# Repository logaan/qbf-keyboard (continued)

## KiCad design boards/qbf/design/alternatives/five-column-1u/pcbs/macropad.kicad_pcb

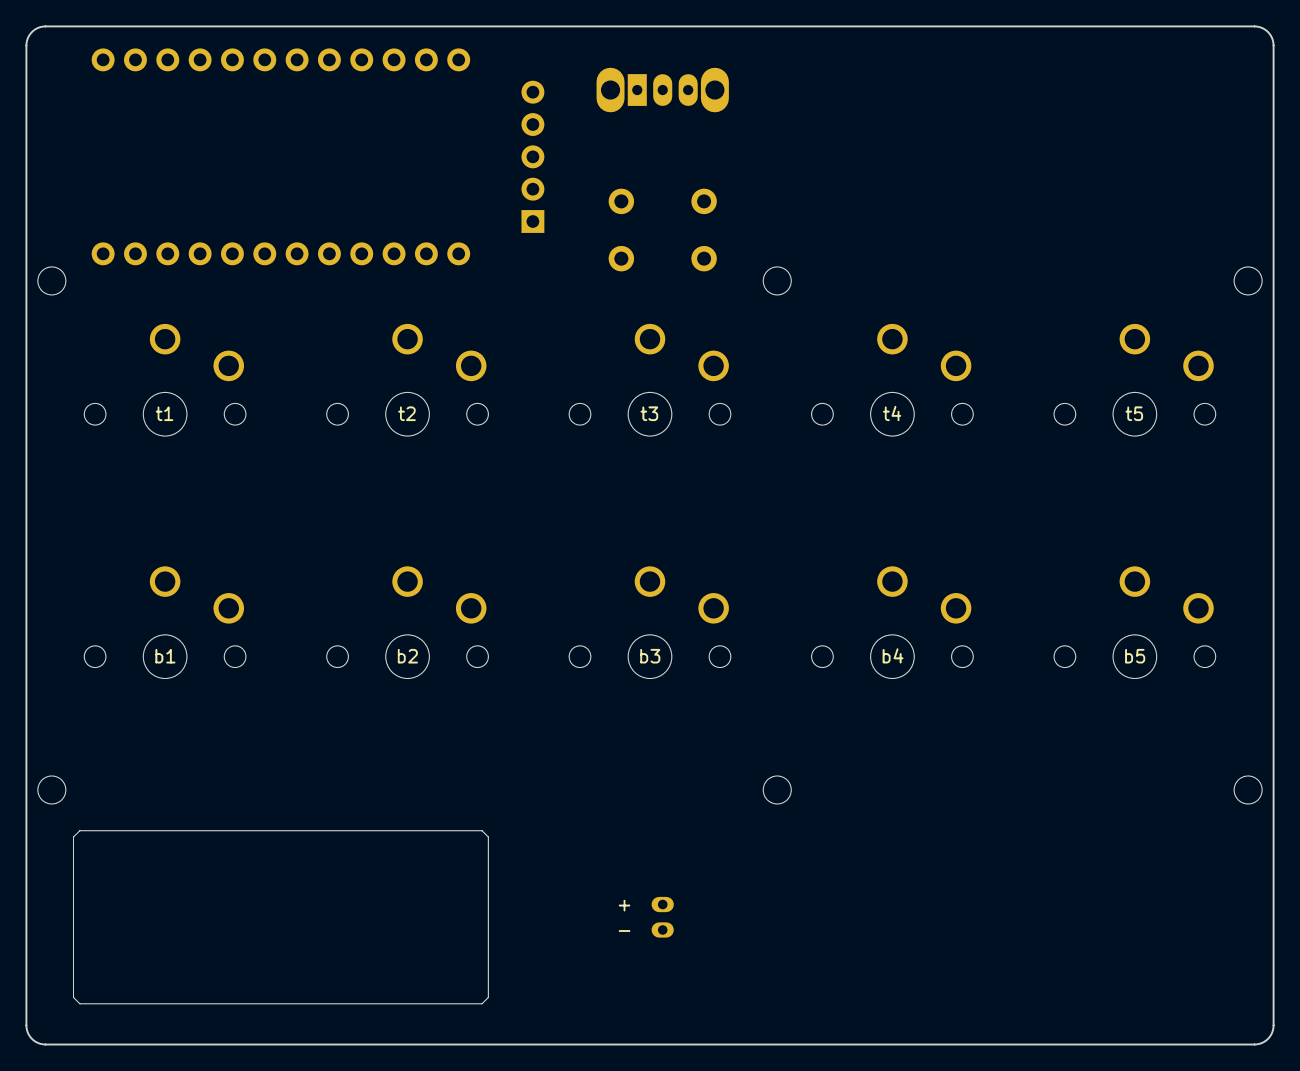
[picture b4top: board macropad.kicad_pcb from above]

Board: 2 copper layers, 98.0 x 80.0 mm, 23 parts (0 on the bottom side), 18 nets, no tracks yet.

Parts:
BAT1: 301230 110mAh max 32x13x3.5 z=-1.4; Protected_301230_Battery_Envelope
H1, H2, H3, H4, H5, H6: M2 mount; M2_Mount
J1: JST-PH S2B-PH-K-S; JST_PH_S2B_PH_K_Horizontal
LCD1: nice!view; Nice_View_Socketed_Module
MCU1: nice!nano v2; Nice_Nano_V2
PWR1: OS102011MS2QN1; CK_OS102011MS2QN1
RST1: 6mm top-actuated tactile; SW_PUSH_6mm_H4_3mm
S1, S2, S3, S4, S5, S6, S7, S8, S9, S10: Choc v1 1U; PG1350_1U
WELL1: Battery well 32.6x13.6; Battery_Well

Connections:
3V3: LCD1.3, MCU1.21
BAT_POS: J1.1, PWR1.1
GND: J1.2, LCD1.4, MCU1.3, MCU1.4, MCU1.23, RST1.2, S1.1, S2.1, S3.1, S4.1, S5.2, S6.2, S7.2, S8.2, S9.1, S10.2
LCD_CLK: LCD1.2, MCU1.6
LCD_CS: LCD1.5, MCU1.1
LCD_SI: LCD1.1, MCU1.5
P4: MCU1.7, S1.2
P5: MCU1.8, S2.2
P6: MCU1.9, S3.2
P7: MCU1.10, S4.2
P8: MCU1.11, S9.2
P9: MCU1.12, S5.1
P10: MCU1.13, S6.1
P14: MCU1.15, S8.1
P15: MCU1.16, S10.1
P16: MCU1.14, S7.1
RST: MCU1.22, RST1.1
VBAT: MCU1.24, PWR1.2
